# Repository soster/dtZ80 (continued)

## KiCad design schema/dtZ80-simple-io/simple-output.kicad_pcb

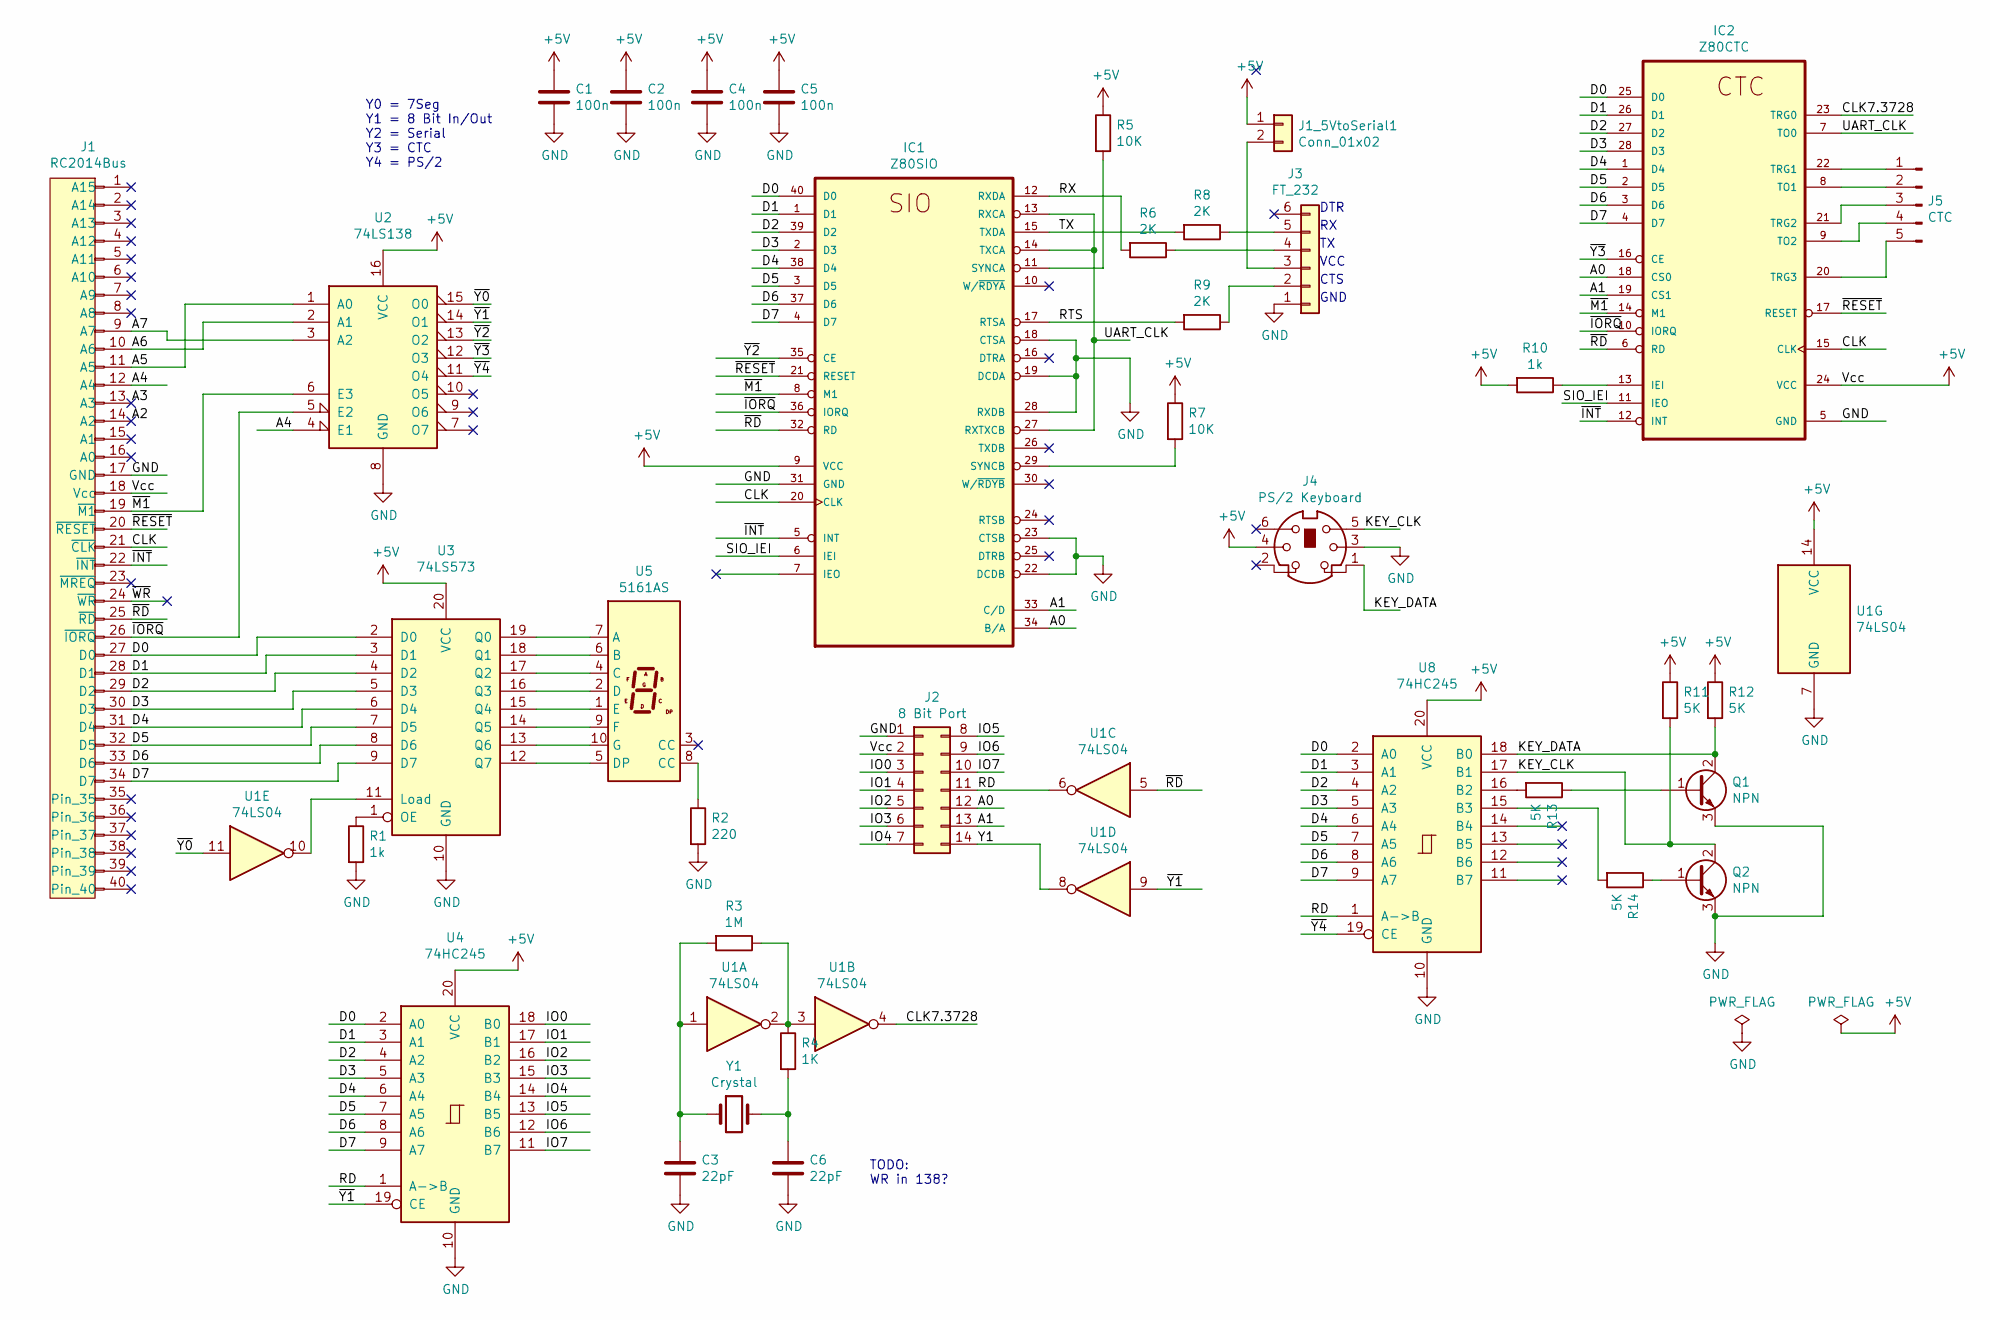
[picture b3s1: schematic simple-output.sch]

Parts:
C1, C2, C4, C5: 100n; C_Disc_D4.3mm_W1.9mm_P5.00mm
C3, C6: 22pF; C_Disc_D4.3mm_W1.9mm_P5.00mm
IC1: Z80SIO; DIP-40_W15.24mm_Socket
IC2: Z80CTC; DIP-28_W15.24mm_Socket
J1: RC2014Bus; PinHeader_1x40_P2.54mm_Vertical
J1_5VtoSerial1: Conn_01x02; PinHeader_1x02_P2.54mm_Vertical
J2: 8 Bit Port; PinHeader_2x07_P2.54mm_Vertical
J3: FT_232; PinHeader_1x06_P2.54mm_Vertical
J4: PS/2 Keyboard; Mini_DIN_6_TE_Connectivity
J5: CTC; PinHeader_1x05_P2.54mm_Vertical
Q1, Q2: NPN; TO-92_HandSolder
R1, R10: 1k; R_Axial_DIN0204_L3.6mm_D1.6mm_P5.08mm_Horizontal
R2: 220; R_Axial_DIN0204_L3.6mm_D1.6mm_P5.08mm_Horizontal
R3: 1M; R_Axial_DIN0204_L3.6mm_D1.6mm_P5.08mm_Horizontal
R4: 1K; R_Axial_DIN0204_L3.6mm_D1.6mm_P5.08mm_Horizontal
R5, R7: 10K; R_Axial_DIN0204_L3.6mm_D1.6mm_P5.08mm_Horizontal
R6, R8, R9: 2K; R_Axial_DIN0204_L3.6mm_D1.6mm_P5.08mm_Horizontal
R11, R12, R13, R14: 5K; R_Axial_DIN0204_L3.6mm_D1.6mm_P5.08mm_Horizontal
U1: 74LS04; DIP-14_W7.62mm_Socket
U2: 74LS138; DIP-16_W7.62mm_Socket
U3: 74LS573; DIP-20_W7.62mm_Socket
U4, U8: 74HC245; DIP-20_W7.62mm_Socket
U5: 5161AS; 7SegmentLED_LTS6760_LTS6780
Y1: Crystal; Crystal_HC49-U_Vertical

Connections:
+5V: C1.1, C2.1, C4.1, C5.1, IC1.9 (VCC), IC2.24 (VCC), J1.18 (Vcc), J1_5VtoSerial1.1, J2.2, J4.4, R5.1, R7.1, R10.2, R11.1, R12.1, U1.14 (VCC), U2.16 (VCC), U3.20 (VCC), U4.20 (VCC), U8.20 (VCC)
/A0: IC1.34 (B/A), IC2.18 (CS0), J1.16 (A0), J2.12
/A1: IC1.33 (C/D), IC2.19 (CS1), J1.15 (A1), J2.13
/A4: J1.12 (A4), U2.4 (E1)
/A5: J1.11 (A5), U2.1 (A0)
/A6: J1.10 (A6), U2.2 (A1)
/A7: J1.9 (A7), U2.3 (A2)
/CLK: IC1.20 (CLK), IC2.15 (CLK), J1.21 (~CLK~)
/CLK7.3728: IC2.23 (TRG0), U1.4
/D0: IC1.40 (D0), IC2.25 (D0), J1.27 (D0), U3.2 (D0), U4.2 (A0), U8.2 (A0)
/D1: IC1.1 (D1), IC2.26 (D1), J1.28 (D1), U3.3 (D1), U4.3 (A1), U8.3 (A1)
/D2: IC1.39 (D2), IC2.27 (D2), J1.29 (D2), U3.4 (D2), U4.4 (A2), U8.4 (A2)
/D3: IC1.2 (D3), IC2.28 (D3), J1.30 (D3), U3.5 (D3), U4.5 (A3), U8.5 (A3)
/D4: IC1.38 (D4), IC2.1 (D4), J1.31 (D4), U3.6 (D4), U4.6 (A4), U8.6 (A4)
/D5: IC1.3 (D5), IC2.2 (D5), J1.32 (D5), U3.7 (D5), U4.7 (A5), U8.7 (A5)
/D6: IC1.37 (D6), IC2.3 (D6), J1.33 (D6), U3.8 (D6), U4.8 (A6), U8.8 (A6)
/D7: IC1.4 (D7), IC2.4 (D7), J1.34 (D7), U3.9 (D7), U4.9 (A7), U8.9 (A7)
/IO0: J2.3, U4.18 (B0)
/IO1: J2.4, U4.17 (B1)
/IO2: J2.5, U4.16 (B2)
/IO3: J2.6, U4.15 (B3)
/IO4: J2.7, U4.14 (B4)
/IO5: J2.8, U4.13 (B5)
/IO6: J2.9, U4.12 (B6)
/IO7: J2.10, U4.11 (B7)
/KEY_CLK: J4.5, Q2.2 (C), R11.2, U8.17 (B1)
/KEY_DATA: J4.1, Q1.2 (C), R12.2, U8.18 (B0)
/RD: J2.11, U1.6, U4.1 (A->B), U8.1 (A->B)
/RTS: IC1.17 (RTSA), R9.2
/RX: IC1.12 (RXDA), R6.2
/SIO_IEI: IC1.6 (IEI), IC2.11 (IEO)
/TX: IC1.15 (TXDA), R8.2
/UART_CLK: IC1.13 (RXCA), IC1.14 (TXCA), IC1.27 (RXTXCB), IC2.7 (TO0)
/Y1: J2.14, U1.8
/~INT~: IC1.5 (INT), IC2.12 (INT), J1.22 (~INT~)
/~IORQ~: IC1.36 (IORQ), IC2.10 (IORQ), J1.26 (~IORQ~), U2.5 (E2)
/~M1~: IC1.8 (M1), IC2.14 (M1), J1.19 (~M1~), U2.6 (E3)
/~RD~: IC1.32 (RD), IC2.6 (RD), J1.25 (~RD~), U1.5
/~RESET~: IC1.21 (RESET), IC2.17 (RESET), J1.20 (~RESET~)
/~Y0~: U1.11, U2.15 (O0)
/~Y1~: U1.9, U2.14 (O1), U4.19 (CE)
/~Y2~: IC1.35 (CE), U2.13 (O2)
/~Y3~: IC2.16 (CE), U2.12 (O3)
/~Y4~: U2.11 (O4), U8.19 (CE)
GND: C1.2, C2.2, C3.2, C4.2, C5.2, C6.2, IC1.18 (CTSA), IC1.19 (DCDA), IC1.22 (DCDB), IC1.23 (CTSB), IC1.28 (RXDB), IC1.31 (GND), IC2.5 (GND), J1.17 (GND), J2.1, J3.1, J4.3, Q1.3 (E), Q2.3 (E), R1.2, R2.2, U1.7 (GND), U2.8 (GND), U3.10 (GND), U4.10 (GND), U8.10 (GND)
unnamed: C3.1, R3.2, U1.1, Y1.1
unnamed: C6.1, R4.2, Y1.2
unnamed: IC1.11 (SYNCA), R5.2
unnamed: IC1.29 (SYNCB), R7.2
unnamed: IC2.8 (TO1), J5.2
unnamed: IC2.9 (TO2), J5.4
unnamed: IC2.13 (IEI), R10.1
unnamed: IC2.20 (TRG3), J5.5
unnamed: IC2.21 (TRG2), J5.3
unnamed: IC2.22 (TRG1), J5.1
unnamed: J1_5VtoSerial1.2, J3.3
unnamed: J3.2, R9.1
unnamed: J3.4, R6.1
unnamed: J3.5, R8.1
unnamed: Q1.1 (B), R13.1
unnamed: Q2.1 (B), R14.1
unnamed: R1.1, U3.1 (OE)
unnamed: R2.1, U5.8 (CC)
unnamed: R3.1, R4.1, U1.2, U1.3
unnamed: R13.2, U8.16 (B2)
unnamed: R14.2, U8.15 (B3)
unnamed: U1.10, U3.11 (Load)
unnamed: U3.12 (Q7), U5.5 (DP)
unnamed: U3.13 (Q6), U5.10 (G)
unnamed: U3.14 (Q5), U5.9 (F)
unnamed: U3.15 (Q4), U5.1 (E)
unnamed: U3.16 (Q3), U5.2 (D)
unnamed: U3.17 (Q2), U5.4 (C)
unnamed: U3.18 (Q1), U5.6 (B)
unnamed: U3.19 (Q0), U5.7 (A)

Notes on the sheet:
TODO: WR in 138?
Y0 = 7Seg Y1 = 8 Bit In/Out Y2 = Serial Y3 = CTC Y4 = PS/2
DTR
VCC
CTS
GND

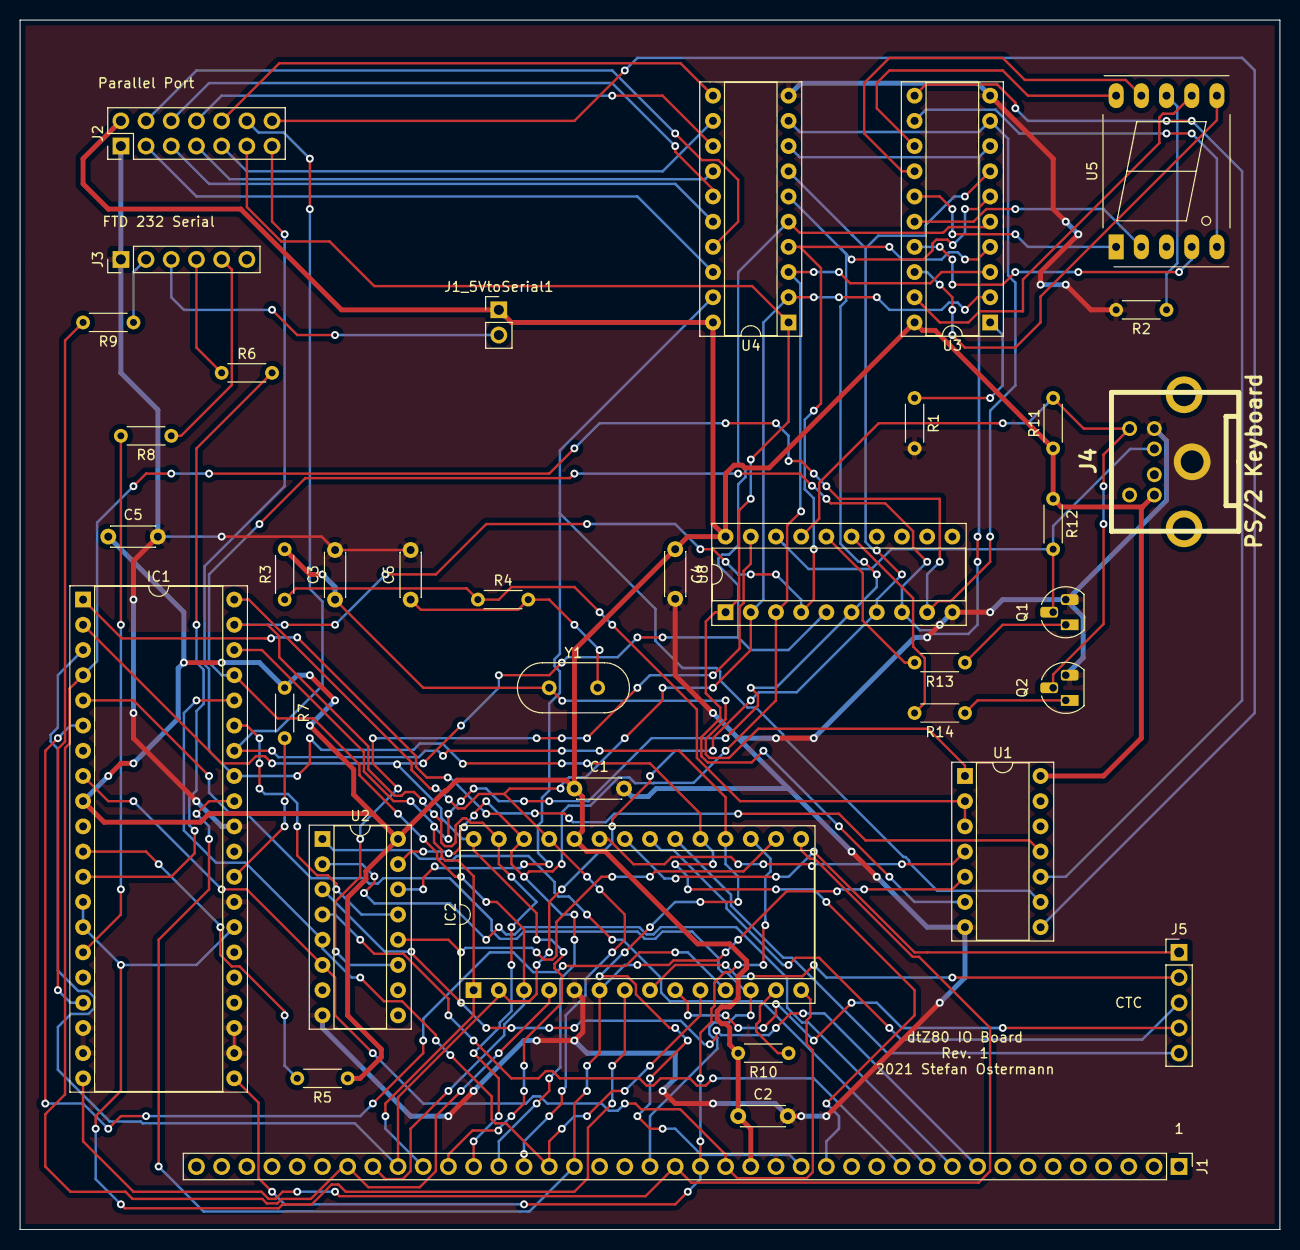
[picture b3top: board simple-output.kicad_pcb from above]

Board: 2 copper layers, 127.0 x 121.9 mm, 37 parts (0 on the bottom side), 75 nets.

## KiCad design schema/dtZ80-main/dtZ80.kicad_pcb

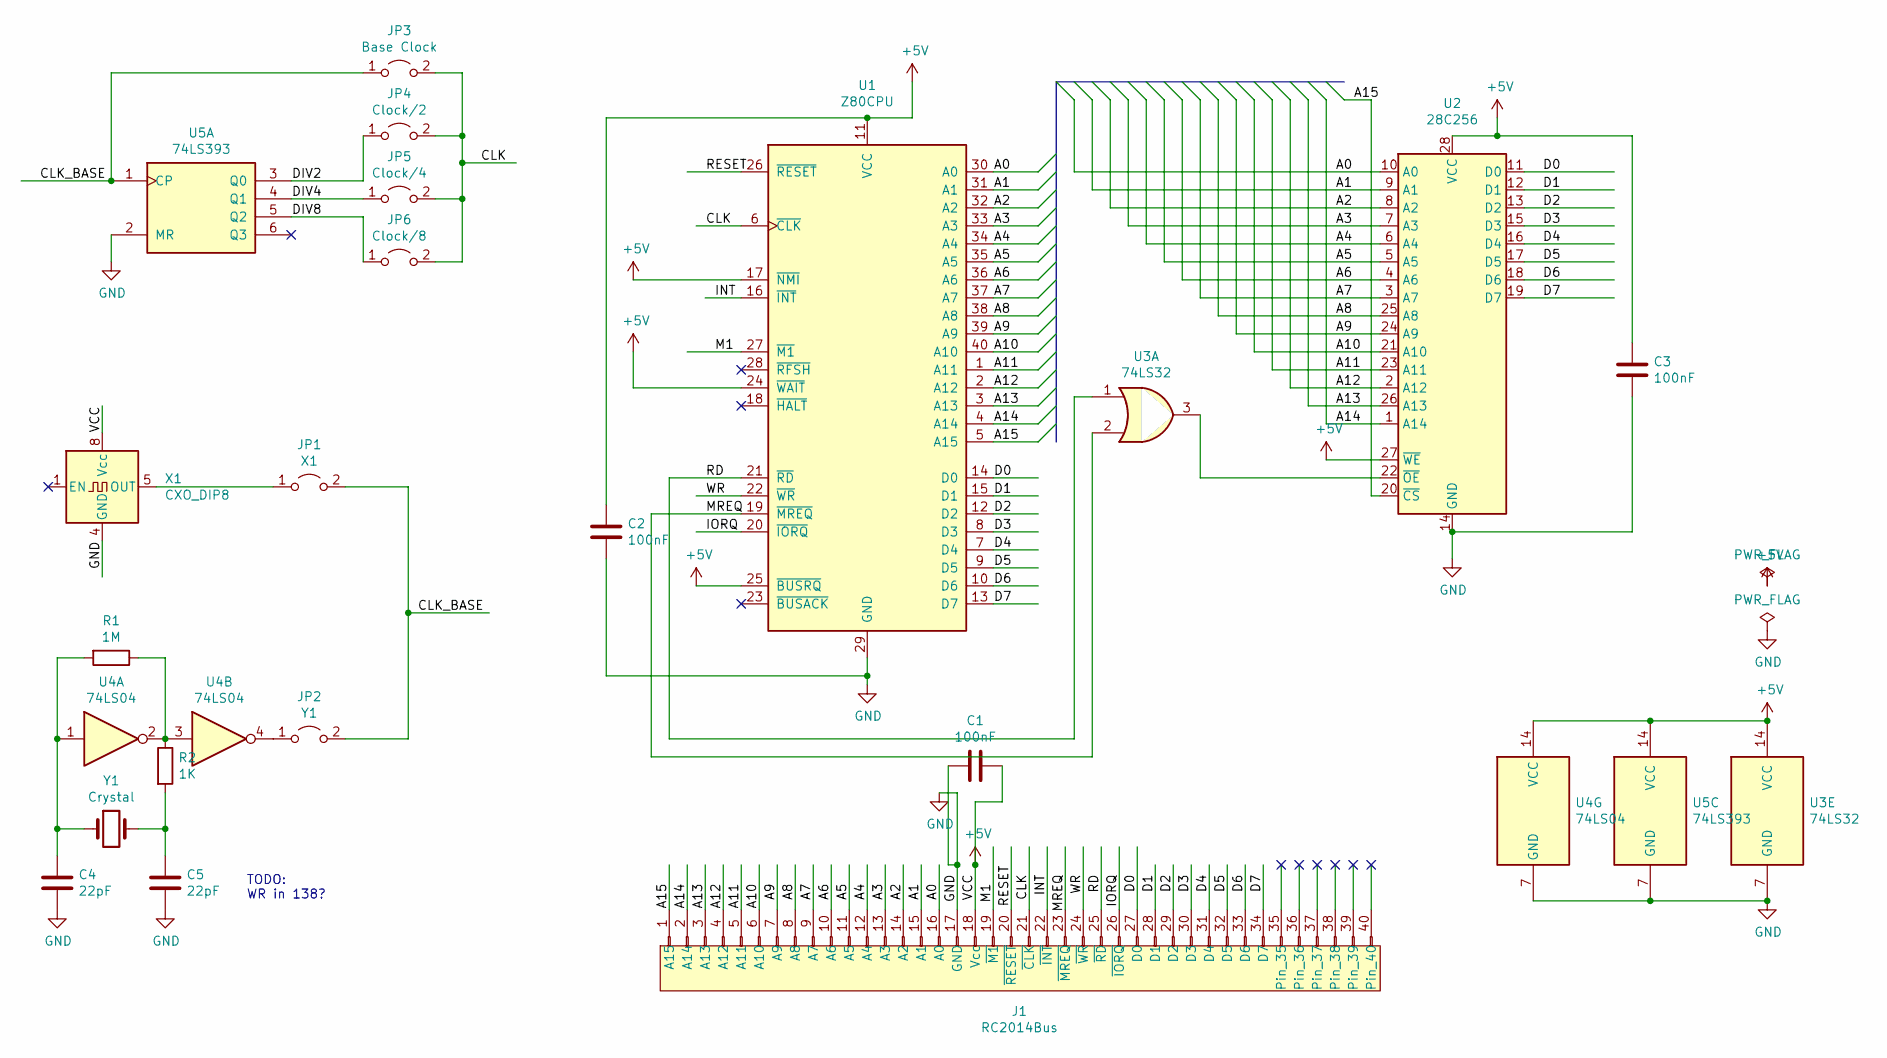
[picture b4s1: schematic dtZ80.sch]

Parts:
C1, C2, C3: 100nF; C_Disc_D3.0mm_W2.0mm_P2.50mm
C4, C5: 22pF; C_Disc_D4.3mm_W1.9mm_P5.00mm
J1: RC2014Bus; PinHeader_1x40_P2.54mm_Vertical
JP1: X1; PinHeader_1x02_P2.54mm_Vertical
JP2: Y1; PinHeader_1x02_P2.54mm_Vertical
JP3: Base Clock; PinHeader_1x02_P2.54mm_Vertical
JP4: Clock/2; PinHeader_1x02_P2.54mm_Vertical
JP5: Clock/4; PinHeader_1x02_P2.54mm_Vertical
JP6: Clock/8; PinHeader_1x02_P2.54mm_Vertical
R1: 1M; R_Axial_DIN0204_L3.6mm_D1.6mm_P5.08mm_Horizontal
R2: 1K; R_Axial_DIN0204_L3.6mm_D1.6mm_P5.08mm_Horizontal
U1: Z80CPU; DIP-40_W15.24mm
U2: 28C256; DIP-28_W15.24mm_Socket_Large_Holes
U3: 74LS32; DIP-14_W7.62mm
U4: 74LS04; DIP-14_W7.62mm_Socket
U5: 74LS393; DIP-14_W7.62mm_Socket
X1: CXO_DIP8; Oscillator_DIP-8
Y1: Crystal; Crystal_HC52-8mm_Vertical

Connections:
+5V: C1.1, C2.2, C3.2, J1.18 (Vcc), U1.11 (VCC), U1.17 (~NMI~), U1.24 (~WAIT~), U1.25 (~BUSRQ~), U2.27 (~WE), U2.28 (VCC), U3.14 (VCC), U4.14 (VCC), U5.14 (VCC), X1.8 (Vcc)
/A0: J1.16 (A0), U1.30 (A0), U2.10 (A0)
/A1: J1.15 (A1), U1.31 (A1), U2.9 (A1)
/A2: J1.14 (A2), U1.32 (A2), U2.8 (A2)
/A3: J1.13 (A3), U1.33 (A3), U2.7 (A3)
/A4: J1.12 (A4), U1.34 (A4), U2.6 (A4)
/A5: J1.11 (A5), U1.35 (A5), U2.5 (A5)
/A6: J1.10 (A6), U1.36 (A6), U2.4 (A6)
/A7: J1.9 (A7), U1.37 (A7), U2.3 (A7)
/A8: J1.8 (A8), U1.38 (A8), U2.25 (A8)
/A9: J1.7 (A9), U1.39 (A9), U2.24 (A9)
/A10: J1.6 (A10), U1.40 (A10), U2.21 (A10)
/A11: J1.5 (A11), U1.1 (A11), U2.23 (A11)
/A12: J1.4 (A12), U1.2 (A12), U2.2 (A12)
/A13: J1.3 (A13), U1.3 (A13), U2.26 (A13)
/A14: J1.2 (A14), U1.4 (A14), U2.1 (A14)
/A15: J1.1 (A15), U1.5 (A15), U2.20 (~CS)
/CLK: J1.21 (~CLK~), JP3.2 (B), JP4.2 (B), JP5.2 (B), JP6.2 (B), U1.6 (~CLK~)
/CLK_BASE: JP1.2 (B), JP2.2 (B), JP3.1 (A), U5.1 (CP)
/D0: J1.27 (D0), U1.14 (D0), U2.11 (D0)
/D1: J1.28 (D1), U1.15 (D1), U2.12 (D1)
/D2: J1.29 (D2), U1.12 (D2), U2.13 (D2)
/D3: J1.30 (D3), U1.8 (D3), U2.15 (D3)
/D4: J1.31 (D4), U1.7 (D4), U2.16 (D4)
/D5: J1.32 (D5), U1.9 (D5), U2.17 (D5)
/D6: J1.33 (D6), U1.10 (D6), U2.18 (D6)
/D7: J1.34 (D7), U1.13 (D7), U2.19 (D7)
/DIV2: JP4.1 (A), U5.3 (Q0)
/DIV4: JP5.1 (A), U5.4 (Q1)
/DIV8: JP6.1 (A), U5.5 (Q2)
/INT: J1.22 (~INT~), U1.16 (~INT~)
/IORQ: J1.26 (~IORQ~), U1.20 (~IORQ~)
/M1: J1.19 (~M1~), U1.27 (~M1~)
/MREQ: J1.23 (~MREQ~), U1.19 (~MREQ~), U3.2
/RD: J1.25 (~RD~), U1.21 (~RD~), U3.1
/RESET: J1.20 (~RESET~), U1.26 (~RESET~)
/WR: J1.24 (~WR~), U1.22 (~WR~)
GND: C1.2, C2.1, C3.1, C4.2, C5.2, J1.17 (GND), U1.29 (GND), U2.14 (GND), U3.7 (GND), U4.7 (GND), U5.2 (MR), U5.7 (GND), X1.4 (GND)
unnamed: C4.1, R1.2, U4.1, Y1.1
unnamed: C5.1, R2.2, Y1.2
unnamed: JP1.1 (A), X1.5 (OUT)
unnamed: JP2.1 (A), U4.4
unnamed: R1.1, R2.1, U4.2, U4.3
unnamed: U2.22 (~OE), U3.3

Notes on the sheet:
TODO: WR in 138?

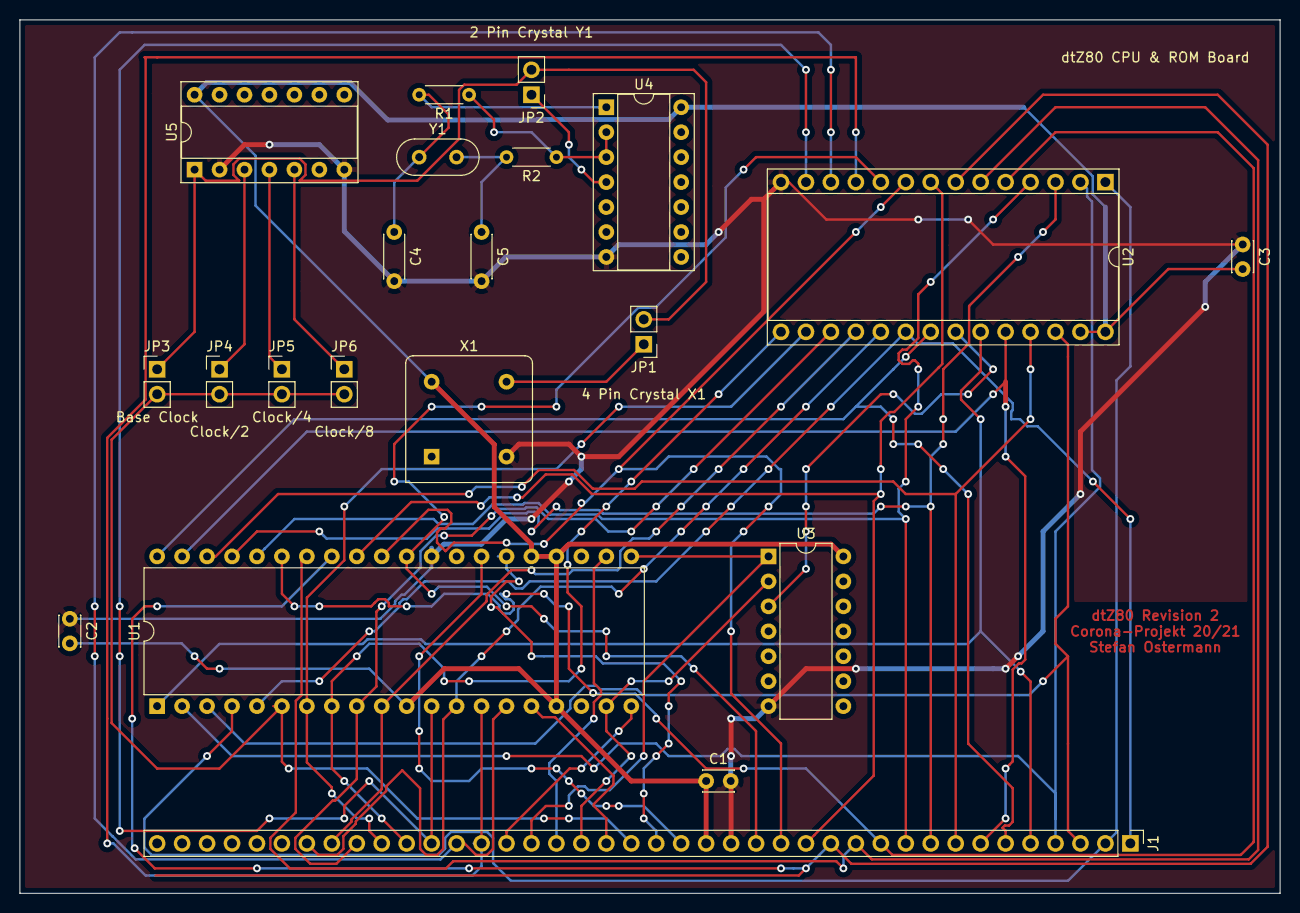
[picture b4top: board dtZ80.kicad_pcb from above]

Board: 2 copper layers, 128.3 x 88.9 mm, 21 parts (0 on the bottom side), 44 nets.

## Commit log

2021-01-02 Readme and images
2021-01-10 more assembler
2021-02-06 Reworked Boards
2021-02-18 First version with sound
2021-02-18 Music Player works!
2021-02-18 Schema
2021-02-28 IO Board Rev 1
2021-02-28 Added ghostbusters
2021-02-28 Datasheets added
2021-02-28 Documentation
2021-02-28 Readme
2021-03-01 CTC & Fixes on IO Board
2021-03-04 SIO, cleanups
2021-03-04 Cleanup
2021-03-04 Serial interface improved
2021-03-07 PS/2 ASM
2021-03-31 Not yet working ps2 -> serial
2021-04-05 More work on PS/2 keyboard
2021-04-09 PS/2 over serial working!
2021-04-11 reset circuit
2021-04-25 schema, datasheets etc
2021-05-04 full schema
2021-05-06 Schema completet
2021-05-06 gerber files
2021-05-06 Cleanups, PDF-Exports
2021-05-19 complete schema, first assembler tests
2021-05-20 integrated version
2021-05-24 Black dtZ80 complete board and ASM code
2021-05-24 New Image
2021-06-21 ASM Player with keyboard
2021-06-23 working music selector
2021-06-23 Improved 8 Bit Sound Player
2021-12-01 info 4 line display
2021-12-05 restructuring, 4 lines lcd working
2021-12-05 4 lines with wrapping
2021-12-05 Test lib fixed
2021-12-08 first barely working bios version
2021-12-08 formatting
2021-12-21 First working bios
2021-12-22 special keys
2021-12-22 lcd datasheet
2022-08-25 Bios accepts serial input from terminal
2022-08-26 Cleanups, CRLF via serial when enter
2022-08-27 Formatting, Cleanups, Fixing asm errors
2022-08-27 simulator
2022-08-28 cleanups, simulator preparations
2022-08-28 reworked serial+keyboard
2022-08-28 debug mode
2022-08-28 simulate string inputs
2022-08-29 beginning opcode recognition
2022-08-29 basic link
2022-08-30 first working opcode
2022-11-09 simulator/emulator
2022-11-19 Changed simulator test to ticks
2023-02-26 WIP music player in bios
2023-02-27 WIP music player
2025-08-04 ai improvements, case
2025-08-05 fixed ai errors
2025-08-05 init sound
